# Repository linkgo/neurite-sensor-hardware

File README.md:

[English](#) | [中文](#)

# Neurite Sensor

The sensor hardware based on esp8266 powered by [Neurite](https://github.com/linkgo/neurite) firmware.  
Originally we use nodemcu lua scripts until we were hardly able to work around the memory issues.

## Demo

As a demo scenario, we put some modules in our office, collecting realtime data.  
Jump: [lab of linkgo.io](http://lab.linkgo.io)

## License

> The MIT License (MIT)
>
> Copyright (c) 2015-2016 Linkgo LLC
>
> Permission is hereby granted, free of charge, to any person obtaining a copy
> of this software and associated documentation files (the "Software"), to deal
> in the Software without restriction, including without limitation the rights
> to use, copy, modify, merge, publish, distribute, sublicense, and/or sell
> copies of the Software, and to permit persons to whom the Software is
> furnished to do so, subject to the following conditions:
>
> The above copyright notice and this permission notice shall be included in all
> copies or substantial portions of the Software.
>
> THE SOFTWARE IS PROVIDED "AS IS", WITHOUT WARRANTY OF ANY KIND, EXPRESS OR
> IMPLIED, INCLUDING BUT NOT LIMITED TO THE WARRANTIES OF MERCHANTABILITY,
> FITNESS FOR A PARTICULAR PURPOSE AND NONINFRINGEMENT. IN NO EVENT SHALL THE
> AUTHORS OR COPYRIGHT HOLDERS BE LIABLE FOR ANY CLAIM, DAMAGES OR OTHER
> LIABILITY, WHETHER IN AN ACTION OF CONTRACT, TORT OR OTHERWISE, ARISING FROM,
> OUT OF OR IN CONNECTION WITH THE SOFTWARE OR THE USE OR OTHER DEALINGS IN THE
> SOFTWARE.

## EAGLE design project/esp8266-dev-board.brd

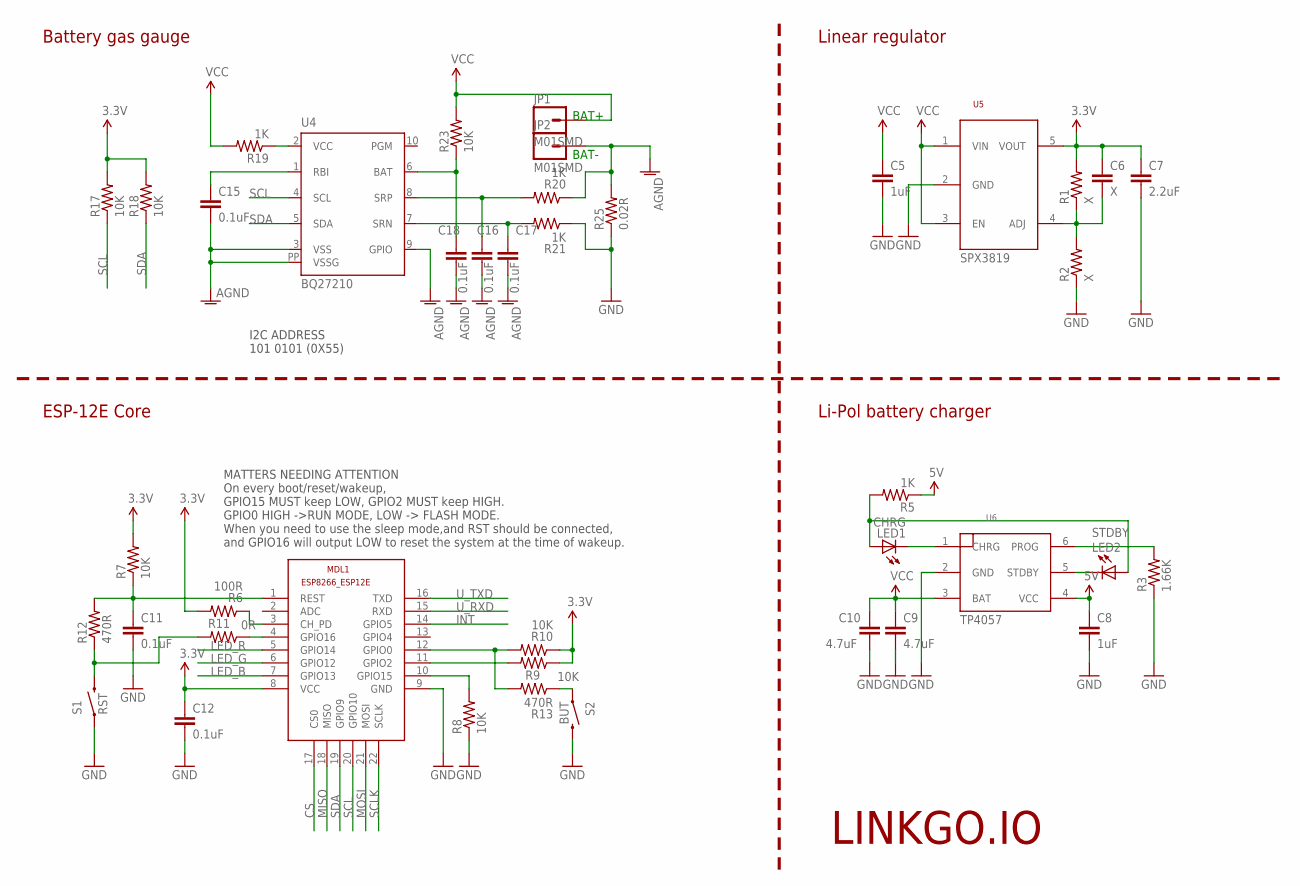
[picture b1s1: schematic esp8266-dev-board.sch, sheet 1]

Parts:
C5, C8: 1uF; 0603-CAP
C6: X; 0603-CAP
C7: 2.2uF; 0603-CAP
C9, C10: 4.7uF; 0603-CAP
C11, C12, C15, C16, C17, C18: 0.1uF; 0603-CAP
JP1, JP2: M01SMD; LUXEON-PAD
LED1: CHRG; LED-0603
LED2: STDBY; LED-0603
MDL1: ESP8266-12EESP8266-ESP12E; ESP8266-ESP12E
R1, R2: X; 0603-RES
R3: 1.66K; 0603-RES
R5, R19, R20, R21: 1K; 0603-RES
R6: 100R; 0603-RES
R7, R8, R9, R10, R17, R18, R23: 10K; 0603-RES
R11: 0R; 0603-RES
R12, R13: 470R; 0603-RES
R25: 0.02R; 1206
S1: RST; TACTILE-SWITCH-1101NE
S2: BUT; TACTILE-SWITCH-1101NE
U4: BQ27210; DRK_S-PDSO-N10
U5: SPX3819M5-ADJ; SOT23-5
U6: TP4057; SOT23-6

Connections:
3.3V: C6.1, C7.1, C12.1, MDL1.8 (VCC), R1.2, R6.2, R7.2, R9.1, R10.1, R17.2, R18.2, U5.5 (VOUT); also elsewhere on the board
5V: C8.1, R5.1, U6.4 (VCC); also elsewhere on the board
AGND: C15.2, C16.2, C17.2, C18.2, JP2.P$1, R20.1, R25.2, U4.3 (VSS), U4.9 (GPIO), U4.PP (VSSG)
CS: MDL1.17 (CS0); also elsewhere on the board
GND: C5.2, C7.2, C8.2, C9.2, C10.2, C11.2, C12.2, MDL1.9 (GND), R2.1, R3.1, R8.1, R21.1, R25.1, S1.P$1 (1), S2.P$2 (2), U5.2 (GND), U6.2 (GND); also elsewhere on the board
INT: MDL1.14 (GPIO5); also elsewhere on the board
LED_B: MDL1.7 (GPIO13); also elsewhere on the board
LED_G: MDL1.6 (GPIO12); also elsewhere on the board
LED_R: MDL1.5 (GPIO14); also elsewhere on the board
MISO: MDL1.18 (MISO); also elsewhere on the board
MOSI: MDL1.21 (MOSI); also elsewhere on the board
unnamed: C6.2, R1.1, R2.2, U5.4 (ADJ)
unnamed: MDL1.10 (GPIO15), R8.2
unnamed: MDL1.12 (GPIO0), R10.2, R13.2
unnamed: LED1.A, LED2.A, R5.2
unnamed: C11.1, MDL1.1 (REST), R7.1, R12.2
unnamed: LED1.C, U6.1 (CHRG)
unnamed: LED2.C, U6.5 (STDBY)
unnamed: R3.2, U6.6 (PROG)
unnamed: MDL1.3 (CH_PD), R6.1
unnamed: MDL1.11 (GPIO2), R9.2
unnamed: MDL1.4 (GPIO16), R11.1
unnamed: R11.2, R12.1, S1.P$2 (2)
unnamed: R13.1, S2.P$1 (1)
unnamed: C15.1, U4.1 (RBI)
unnamed: R19.1, U4.2 (VCC)
unnamed: C17.1, R21.2, U4.7 (SRN)
unnamed: C16.1, R20.2, U4.8 (SRP)
unnamed: C18.1, R23.1, U4.6 (BAT)
PP: U4.PP@1 (PP), U4.PP@2 (PP), U4.PP@3 (PP), U4.PP@4 (PP), U4.PP@5 (PP), U4.PP@6 (PP), U4.PP@7 (PP), U4.PP@8 (PP), U4.PP@9 (PP), U4.PP@10 (PP)
SCL: MDL1.20 (GPIO10), R17.1, U4.4 (SCL); also elsewhere on the board
SCLK: MDL1.22 (SCLK); also elsewhere on the board
SDA: MDL1.19 (GPIO9), R18.1, U4.5 (SDA); also elsewhere on the board
U_RXD: MDL1.15 (RXD); also elsewhere on the board
U_TXD: MDL1.16 (TXD); also elsewhere on the board
VCC: C5.1, C9.1, C10.1, JP1.P$1, R19.2, R23.2, U5.1 (VIN), U5.3 (EN), U6.3 (BAT)

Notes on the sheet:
MATTERS NEEDING ATTENTION On every boot/reset/wakeup, GPIO15 MUST keep LOW, GPIO2 MUST keep HIGH. GPIO0 HIGH ->RUN MODE, LOW -> FLASH MODE. When you need to use the sleep mode,and RST should be connected, and GPIO16 will output LOW to reset the system at the time of wakeup.
BAT+
BAT-
Battery gas gauge
Linear regulator
Li-Pol battery charger
ESP-12E Core
I2C ADDRESS 101 0101 (0X55)
LINKGO.IO
SPX3819
TP4057

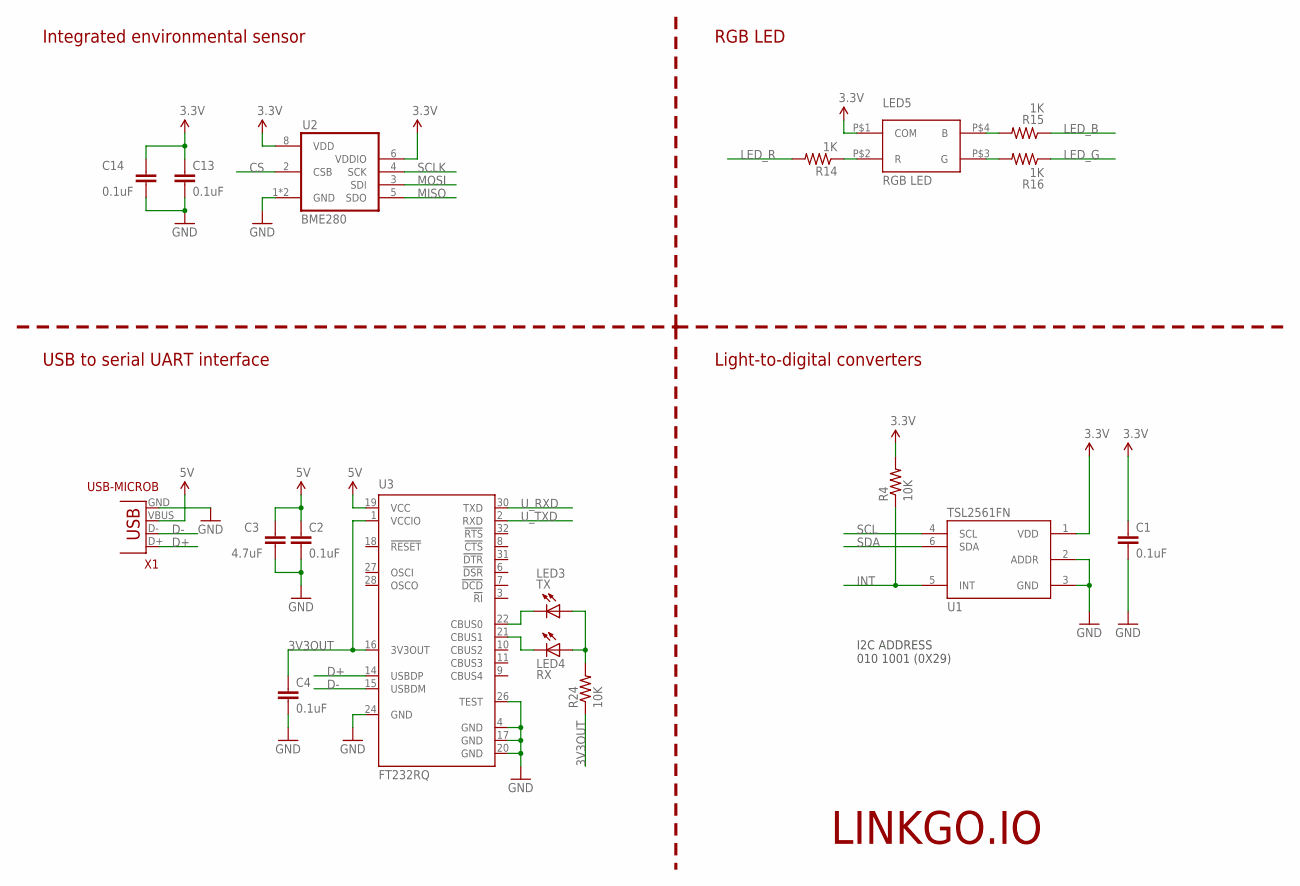
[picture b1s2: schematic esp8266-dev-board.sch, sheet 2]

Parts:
C1, C2, C4, C13, C14: 0.1uF; 0603-CAP
C3: 4.7uF; 0603-CAP
LED3: TX; LED-0603
LED4: RX; LED-0603
LED5: 0603RGB
R4, R24: 10K; 0603-RES
R14, R15, R16: 1K; 0603-RES
U1: TSL2561FN; FN-6
U2: BME280
U3: FT232RQ; QFN32
X1: USB-MICROB

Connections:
3.3V: C1.1, C13.1, C14.1, LED5.P$1 (COM), R4.2, U1.1 (VDD), U2.6 (VDDIO), U2.8 (VDD); also elsewhere on the board
3V3OUT: C4.1, R24.1, U3.1 (VCCIO), U3.16 (3V3OUT)
5V: C2.1, C3.1, U3.19 (VCC), X1.VBUS; also elsewhere on the board
CS: U2.2 (CSB); also elsewhere on the board
D+: U3.14 (USBDP), X1.D+
D-: U3.15 (USBDM), X1.D-
GND: C1.2, C2.2, C3.2, C4.2, C13.2, C14.2, U1.2 (ADDR), U1.3 (GND), U2.1 (GND), U2.7 (GND), U3.4 (GND), U3.17 (GND), U3.20 (GND), U3.24 (GND), U3.26 (TEST), X1.GND; also elsewhere on the board
INT: R4.1, U1.5 (INT); also elsewhere on the board
LED_B: R15.1; also elsewhere on the board
LED_G: R16.1; also elsewhere on the board
LED_R: R14.2; also elsewhere on the board
MISO: U2.5 (SDO); also elsewhere on the board
MOSI: U2.3 (SDI); also elsewhere on the board
unnamed: LED3.C, U3.22 (CBUS0)
unnamed: LED4.C, U3.21 (CBUS1)
unnamed: LED5.P$2 (R), R14.1
unnamed: LED5.P$4 (B), R15.2
unnamed: LED5.P$3 (G), R16.2
unnamed: LED3.A, LED4.A, R24.2
SCL: U1.4 (SCL); also elsewhere on the board
SCLK: U2.4 (SCK); also elsewhere on the board
SDA: U1.6 (SDA); also elsewhere on the board
U_RXD: U3.30 (TXD); also elsewhere on the board
U_TXD: U3.2 (RXD); also elsewhere on the board

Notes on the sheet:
I2C ADDRESS 010 1001 (0X29)
RGB LED
Integrated environmental sensor
USB to serial UART interface
Light-to-digital converters
LINKGO.IO
LED5

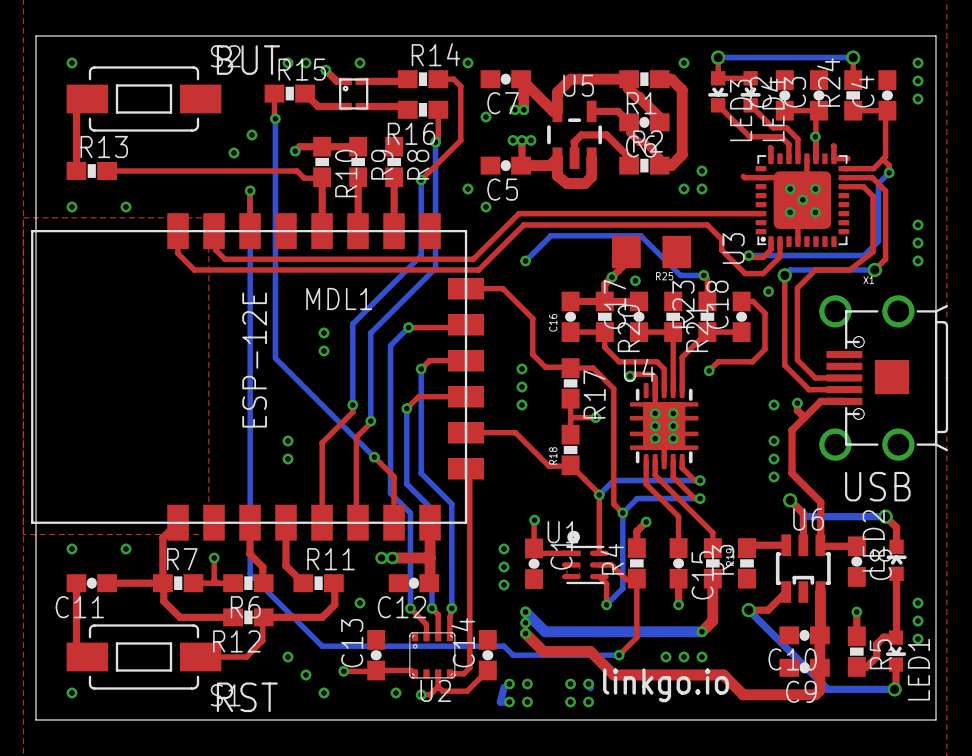
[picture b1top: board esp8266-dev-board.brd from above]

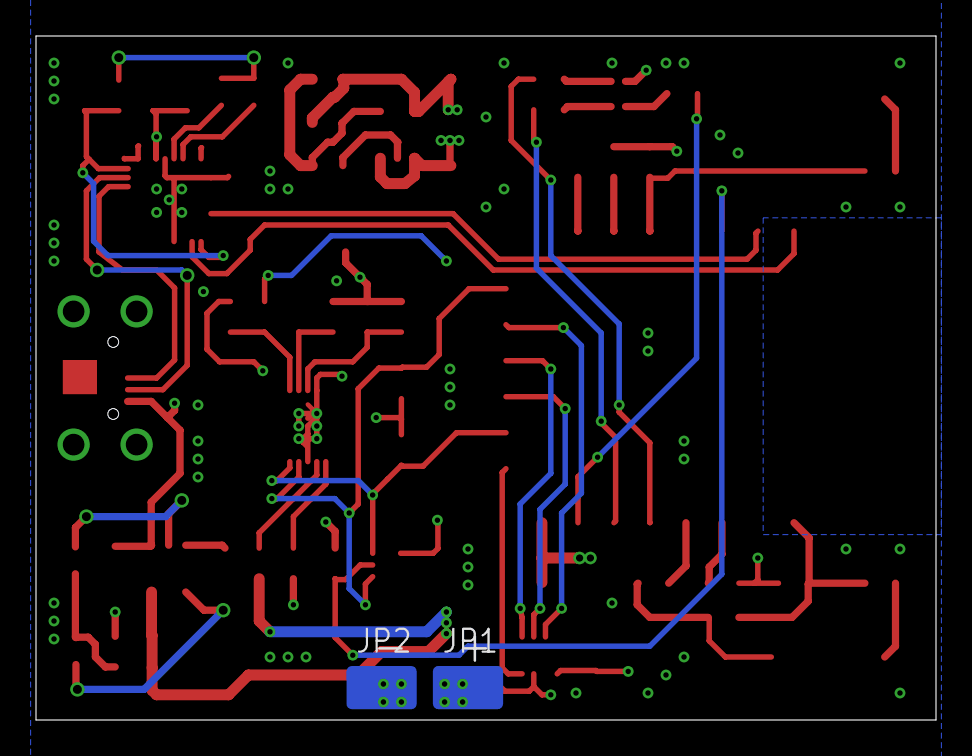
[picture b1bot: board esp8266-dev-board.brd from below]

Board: 4 copper layers, 50.0 x 38.0 mm, 59 parts (2 on the bottom side), 45 nets.

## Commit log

2015-08-19 init commit.
2015-08-21 Add BOM for the project.
2015-08-21 script: add test code
2015-08-21 script: update test scripts
2015-08-21 script: eeprom: avoid potential stack overflow
2015-08-22 script: add README
2015-08-22 script: typo
2015-08-22 script: add lsap to test basic wifi capability
2015-08-25 update rgb led test, init wifi mode to station
2015-08-26 apply scripts for rework version
    assignment:
    gpio14 -- sda
    gpio12 -- scl
2015-08-26 slightly refine
2015-08-27 for byte read, 1000 1010
2015-08-27 add tsl2561 lib
2015-08-27 9600 is default baud
2015-08-27 add button function
2015-08-27 interrupt sucks for button, use tmr, elegantly...
    we can support short press, long press, long long press....
2015-08-27 add late start script
    some module may crash the system if we don't delay its starting like but.lua.
2015-08-27 if but.lua started in rc, any button press crashes...
2015-08-28 reduce frequency of tsl access
2015-08-28 update i2c pin assignment
2015-08-28 use nodemcu-uploader instead of luatool
    a bit more efficient
2015-08-28 fix an error of command to uploading scripts
2015-08-29 add lower power mode
2015-08-29 sleep some time after normal work done
2015-08-29 update sleep control
2015-08-29 unify io name
2015-08-29 config pwm for led
2015-08-30 submit luatool to be an alternative
2015-08-30 add breathing led representing alive working
2015-08-30 some more updates
2015-08-30 a bunch of updates
2015-08-30 set max wifi connecting retry count
2015-08-30 file type -> unix
2015-08-30 do not touch led in but.lua
2015-08-30 update a bit in rc_wifi
2015-08-31 lower cpu usage on led
2015-08-31 run file like function call
2015-08-31 clean up code, compile source to save mem
    1. remove the fat httpserver things, use another method, in:
    rc_wifi.lua
    run_config.lua
    2. remove unused code
    3. replace html file with a new one
2015-08-31 softap wifi config works
    now we can use softap mode to config ssid and password,
    then restart and switch to station mode for normal job.
2015-08-31 typo
2015-08-31 support boot mode switching
    press BUT after reset until led on/off cycle finished,
    to switch between boot modes below:
    1. flag_dsleep == true: enter deep sleep without doing anything
    2. flag_dsleep == false: start normal job, then go to deep sleep
2015-08-31 add comment for compile behavior
2015-08-31 support sleep argument, thus we can customize time
2015-08-31 add LICENSE file
2015-08-31 unify led control, use pwm
2015-08-31 remove trivial print
2015-08-31 reduce prints
2015-08-31 add compiled tsl2561 binary
2015-08-31 add get lux api
2015-09-02 temporary update
2015-09-02 do not compile tsl2561.lua, we have another trick
    Compiling tsl2561.lua results to unexpected memory failure.
    We've did some trick (modified tsl2561.lua) to make it pass
    node.compile(). So just upload the prebuilt tsl2561.lc will be fine.
2015-09-02 add DEBUG mode, in addition to ACTIVE and SLEEP.
    Sometimes we need nothing other than the lua prompt, especiall to debug.
    Since we are on battery all the time, we need to switch among different
    modes according to one single user button, and keep the battery last
    long at the same time.
    Thus, to achieve all three states ACTIVE, SLEEP and DEBUG, we
    designed this flow which can be described as:
2015-09-02 a bit of updates
2015-09-03 add telnet server, more easily debug
2015-09-03 Revert "temporary update"
    This reverts commit 81657ec409f3fbf76c654c0f3a285c8696f0c3fc.
2015-09-06 a bit of update
2015-09-07 memory tuning
2015-09-07 memory tuning done
2015-09-07 rename
2015-09-07 support mqtt
    Temporarily hard coded broker ip and other arguments,
    will update later.
2015-09-07 update tsl2561, remove trivial calculations
2015-09-07 a bunch of update for mqtt automation
    current load: sleep 60s and wake up a bit of time to publish data.
2015-09-08 clean up and save a bit mem, still needs tuning
2015-09-10 t and h ok
2015-09-10 add bme280 support
2015-09-10 sleepy neuron
2015-09-10 prints can't be in tmr callback, but is ok now
2015-09-10 save a bit memory
2015-09-10 make use of file to save memory
2015-09-10 update sensor jobs
2015-09-11 save memory at the expense of efficiency and flash
    Also in this commit we add logic to publish bme280 data.
2015-09-11 separate memory consuming, leave a bit to rc.lua
2015-09-11 make use of async for sensor job while connecting
2015-09-11 don't forget to make it sleep once job done
2015-09-11 if fail to connect, sleep and try at next wake up
    We have this change in order to avoid the case that if the wifi
    signal is not good, esp fails to connect then act as softap forever.
    If we would like to change the ssid information, just keep pressing
    the button when goes into active mode after boot up.
2015-09-11 some cleanups
2015-09-11 reduce normal work timeout to 30s
2016-07-12 save last changes
2016-07-12 add README and img

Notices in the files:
parts and their libraries:
SparkFun-Resistors: Licensing: CC v3.0 Share-Alike You are welcome to use this library for commercial purposes.
SparkFun-DigitalIC: Licensing: Creative Commons ShareAlike 4.0 International - https://creativecommons.org/licenses/by-sa/4.0
